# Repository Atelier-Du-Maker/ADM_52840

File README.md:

# ADM_52840

Proto board for : https://fr.aliexpress.com/store/product/Nordic-nRF52840-Bluetooth-module-grid-development-board-BLE5-0-Bluetooth-serial-low-power-voice-long-distance/420533_32868365660.html

https://atelierdumaker.com/portfolio/nrf52840-breakout-holyiot/

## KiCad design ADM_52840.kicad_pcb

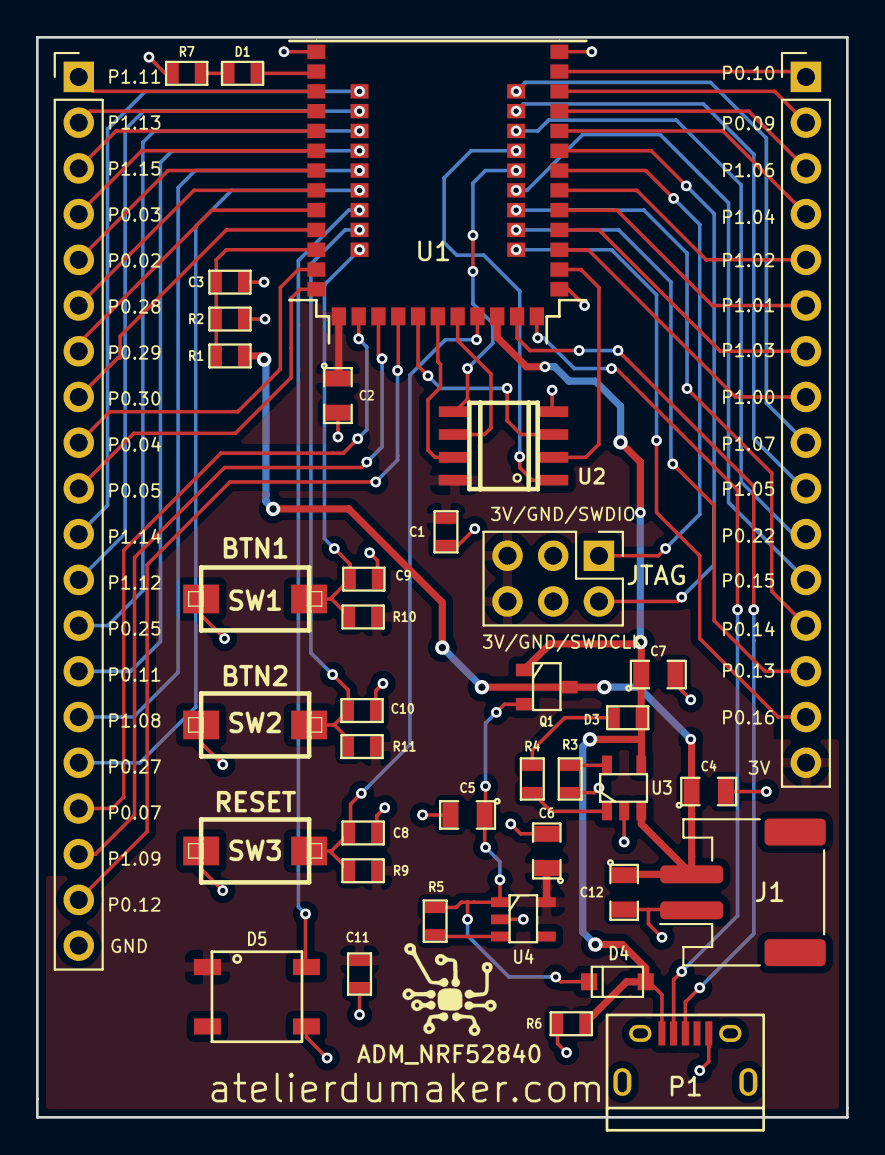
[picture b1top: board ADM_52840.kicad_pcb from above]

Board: 2 copper layers, 45.0 x 60.0 mm, 41 parts (1 on the bottom side), 60 nets.

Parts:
C1, C8, C9, C10, C11: 100nF; SM0603
C2, C4, C5, C6: 10microF; SM0805
C3: 1nF; SM0603
C7, C12: 10uF; SM0805
D1: LED1; SM0603
D3: LED3; SM0603
D4: MBR120; SOD-123
D5: SK6812; WS2812B
G1: LOGO; adm_lite
G2: LOGO; adm
J1: JST; JST_PH_S2B-PH-SM4-TB_1x02-1MP_P2.00mm_Horizontal
J3: Conn_01x16_Male; PinHeader_1x16_P2.54mm_Vertical
J4: Conn_01x20_Male; PinHeader_1x20_P2.54mm_Vertical
J5: JTAG; PinHeader_2x03_P2.54mm_Vertical
P1: USB_micro_B; USB_Micro-B
Q1: DMP2045U; SOT23
R1: 806K; SM0603
R2: 2M; SM0603
R3: 10K; SM0603
R4: 1K; SM0603
R5, R6: 100K; SM0603
R7: 330; SM0603
R9, R10, R11: 10k mini; SM0603
SW1: BTN1; SWITCH_CMS
SW2: BTN2; SWITCH_CMS
SW3: RESET; SWITCH_CMS
U1: HolyIOT_NRF52840; HolyIOT-NRF52840-Module
U2: GD25Q16; SOIC8
U3: MCP73831; SOT23-5
U4: AP2127K-3.3; SOT23-5

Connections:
BAT: C3.1, R1.2, R2.1, U1.11
BTN1: C9.1, R10.1, SW1.2, U1.22
BTN2: C10.1, R11.1, SW2.2, U1.21
D+: P1.3, U1.46
D-: P1.2, U1.45
GND: C1.2, C2.2, C3.2, C4.2, C5.2, C6.2, C7.2, C8.2, C9.2, C10.2, C11.1, C12.2, D5.1, J1.1, J4.20, J5.3, J5.4, P1.5, R2.2, R3.1, R6.1, R7.2, SW1.1, SW2.1, SW3.2, U1.1, U1.32, U1.44, U2.4, U3.2, U4.2
unnamed: C5.1, D4.1, Q1.2, R5.2, U4.1
unnamed: C8.1, R9.1, SW3.1, U1.48
unnamed: D1.1, R7.1
unnamed: D1.2, U1.2
unnamed: D3.1, R4.2
unnamed: J3.1, U1.33
unnamed: J3.2, U1.34
unnamed: J3.3, U1.35
unnamed: J3.4, U1.36
unnamed: J3.5, U1.39
unnamed: J3.6, U1.40
unnamed: J3.7, U1.41
unnamed: J3.8, U1.42
unnamed: J3.9, U1.23
unnamed: J3.10, U1.24
unnamed: J3.11, U1.25
unnamed: J3.12, U1.28
unnamed: J3.13, U1.29
unnamed: J3.14, U1.30
unnamed: J3.15, U1.31
unnamed: J4.1, U1.3
unnamed: J4.2, U1.4
unnamed: J4.3, U1.5
unnamed: J4.4, U1.6
unnamed: J4.5, U1.7
unnamed: J4.6, U1.8
unnamed: J4.7, U1.9
unnamed: J4.8, U1.10
unnamed: J4.9, U1.12
unnamed: J4.10, U1.13
unnamed: J4.11, U1.14
unnamed: J4.12, U1.15
unnamed: J4.13, U1.16
unnamed: J4.14, U1.17
unnamed: J4.15, U1.18
unnamed: J4.16, U1.19
unnamed: J4.17, U1.54
unnamed: J4.18, U1.53
unnamed: J4.19, U1.52
unnamed: R3.2, U3.5
unnamed: R4.1, U3.1
unnamed: R5.1, U4.3
QSPI_0: U1.27, U2.5
QSPI_1: U1.43, U2.2
QSPI_2: U1.51, U2.3
QSPI_3: U1.50, U2.7
QSPI_CLK: U1.49, U2.6
QSPI_CS: U1.26, U2.1
SK_SIGNAL: D5.2, U1.20
SWDCLK: J5.1, U1.38
SWDIO: J5.2, U1.37
VBAT: C4.1, C12.1, J1.2, Q1.3, R1.1, U3.3
VBUS: C7.1, D3.2, D4.2, P1.1, Q1.1, R6.2, U1.47, U3.4
V_NRF: C1.1, C2.1, C6.1, C11.2, D5.3, J3.16, J5.5, J5.6, R9.2, R10.2, R11.2, U1.55, U2.8, U4.5

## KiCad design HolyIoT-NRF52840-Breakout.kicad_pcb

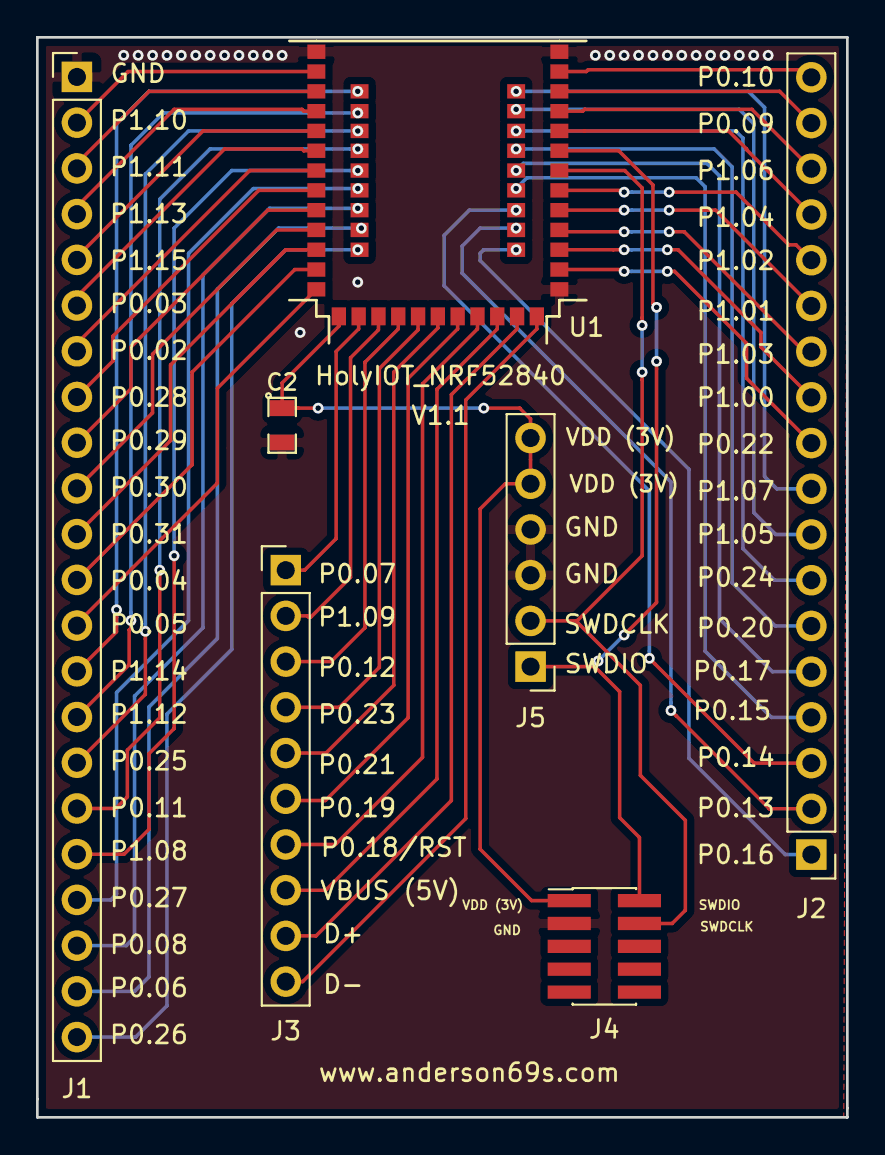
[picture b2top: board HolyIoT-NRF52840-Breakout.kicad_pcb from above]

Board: 2 copper layers, 45.0 x 60.0 mm, 7 parts (0 on the bottom side), 53 nets.

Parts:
C2: C; SM0805
J1: PinHeader_1x22_P2.54mm_Vertical
J2: PinHeader_1x18_P2.54mm_Vertical
J3: PinHeader_1x10_P2.54mm_Vertical
J4: PinHeader_2x05_P1.27mm_Vertical_SMD
J5: PinHeader_1x06_P2.54mm_Vertical
U1: HolyIOT_NRF52840; HolyIOT-NRF52840-Module

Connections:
GND: C2.2, J1.1, J4.3, J5.3, J5.4, U1.1, U1.32, U1.44
unnamed: J1.2, U1.2
unnamed: J1.3, U1.3
unnamed: J1.4, U1.4
unnamed: J1.5, U1.5
unnamed: J1.6, U1.6
unnamed: J1.7, U1.7
unnamed: J1.8, U1.8
unnamed: J1.9, U1.9
unnamed: J1.10, U1.10
unnamed: J1.11, U1.11
unnamed: J1.12, U1.12
unnamed: J1.13, U1.13
unnamed: J1.14, U1.14
unnamed: J1.15, U1.15
unnamed: J1.16, U1.16
unnamed: J1.17, U1.17
unnamed: J1.18, U1.18
unnamed: J1.19, U1.19
unnamed: J1.20, U1.20
unnamed: J1.21, U1.21
unnamed: J1.22, U1.22
unnamed: J2.1, U1.31
unnamed: J2.2, U1.30
unnamed: J2.3, U1.29
unnamed: J2.4, U1.28
unnamed: J2.5, U1.27
unnamed: J2.6, U1.26
unnamed: J2.7, U1.25
unnamed: J2.8, U1.24
unnamed: J2.9, U1.23
unnamed: J2.10, U1.43
unnamed: J2.11, U1.42
unnamed: J2.12, U1.41
unnamed: J2.13, U1.40
unnamed: J2.14, U1.39
unnamed: J2.15, U1.36
unnamed: J2.16, U1.35
unnamed: J2.17, U1.34
unnamed: J2.18, U1.33
unnamed: J3.1, U1.54
unnamed: J3.2, U1.53
unnamed: J3.3, U1.52
unnamed: J3.4, U1.51
unnamed: J3.5, U1.50
unnamed: J3.6, U1.49
unnamed: J3.7, U1.48
unnamed: J3.8, U1.47
unnamed: J3.9, U1.46
unnamed: J3.10, U1.45
SWDCLK: J4.4, J5.2, U1.38
SWDIO: J4.2, J5.1, U1.37
V_NRF: C2.1, J4.1, J5.5, J5.6, U1.55

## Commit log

2018-08-31 Initial Work
    Schema
2018-09-02 Moving On
    add datasheet + finished schematics
2018-09-02 First Routing
    First use if PCBNew on this board
2018-09-02 Routing done
    Last thing to do : labelling
2018-09-03 Add some serigraphie
    Add some serigraphie
2018-09-03 Finish PCB V1.0
    Add missing serigraphie
    test via under pad
2018-09-03 Fornet the netlist
    ^^
2018-09-08 micro-usb b
    add micro-usb
2018-09-10 Morning Routing is always the best...
    - Routing DONE in 2 Layers
    - Verification has to be done before order...
2018-09-13 Generate Gerber
    Generate Gerber
    Rework Edge.Cut
2018-09-22 add 3d model
    add 3D model for the module thank's to @arturo182 on twitter
2018-10-06 Change after Rev 1.0
    Need some check for 1.1
    Do we had some sensors???
2018-10-07 Polish
    Polish
2019-01-31 Going Open-Source
    Need just a check before next prod
2019-02-03 Gerber
    Gerber V1.1
2019-03-10 Regenerate Gerber
2020-10-31 Rename
2020-10-31 update spi
2020-11-01 route & 3D
2020-11-02 update alim
2020-11-02 Seri + Corrections
2020-11-02 Logo
2020-11-02 Add some capa
2020-11-03 route
2020-11-06 Done?
2021-02-27 Pinout SPi
    Rework pinout SPI + SK6812 + Footprint SPI
2021-02-27 modifié : pinout.ods
2021-02-27 New Schematic
    Optimisation for naming the pinout
2021-02-27 Routing
    Made new revision with good pinout for routing
2021-02-28 PCB Routing
    Trying to fit everything now that we have a goal
